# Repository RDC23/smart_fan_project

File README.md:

## Cool Colin - Embedded Systems Smart Fan Project ☀️

**Contributors**: Ross Cathcart, Fraser O'Regan, Ruihang Wang

---

### Overview

This project oversaw the design and construction of a desktop “smart fan” which uses tracking technology to enable the fan to autonomously follow a nearby person, making it ideal for individual use in dynamic workspaces. The tracking mechanism should increase the efficacy in cooling the person by ensuring that it is optimally positioned to promote convective heat loss from the target, reducing heat fatigue and allowing the user to feel more comfortable. 

---

### Project Build

---

### Tracking Mode Demonstration 

https://github.com/RDC23/smart_fan_project/assets/112988260/db7c453c-c118-40b3-909e-dfdff9f8903a

---

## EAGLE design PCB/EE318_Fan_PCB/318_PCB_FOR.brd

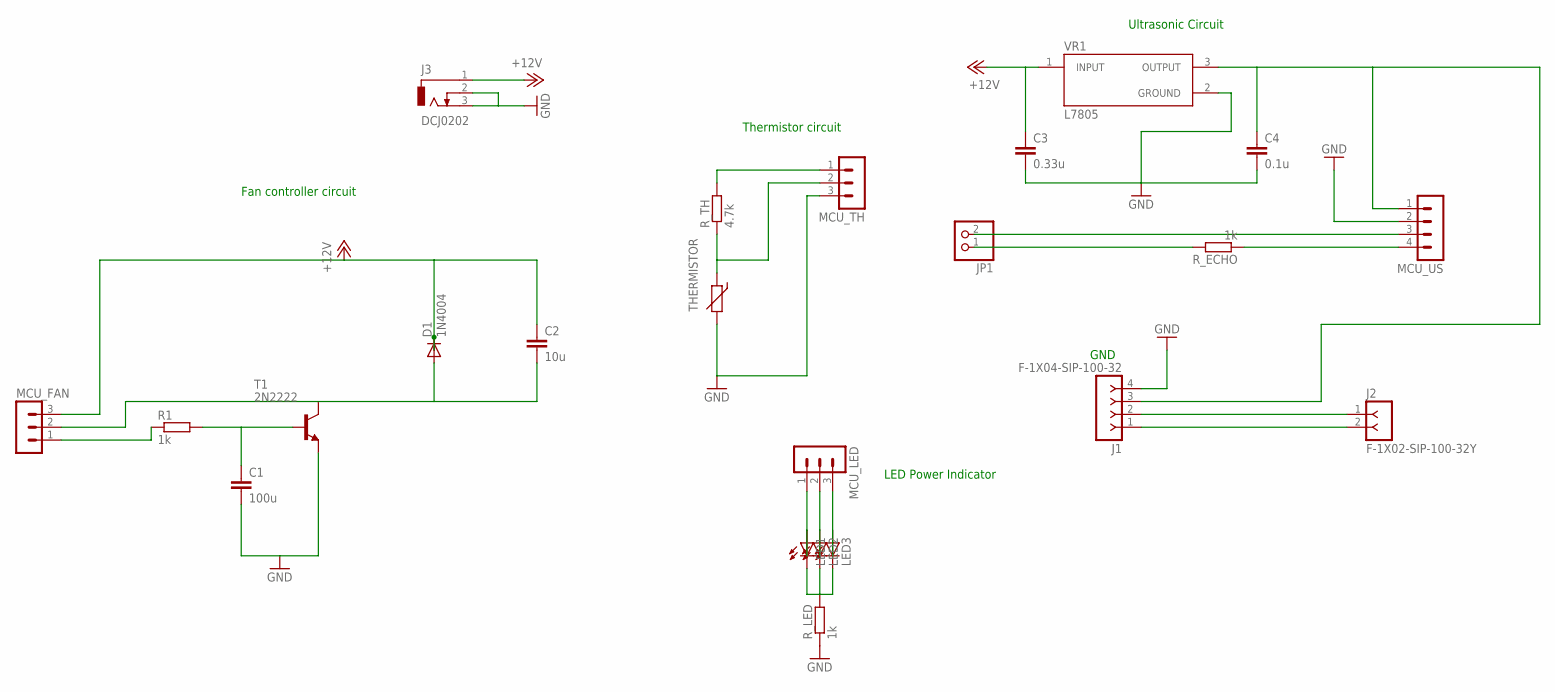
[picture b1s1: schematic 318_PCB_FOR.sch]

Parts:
C1: 100u; C025-025X050
C2: 10u; C025-025X050
C3: 0.33u; C025-025X050
C4: 0.1u; C025-025X050
D1: 1N4004; DO41-10
J1: F-1X04-SIP-100-32; SIP-100-04-32
J2: F-1X02-SIP-100-32Y; SIP-100-02-32Y
J3: DCJ0202
JP1: PINHD-1X2; 1X02
LED1, LED2, LED3: LEDSFH480; SFH480
MCU_FAN: MA03-1
MCU_LED: MA03-1
MCU_TH: MA03-1
MCU_US: MA04-1
R1: 1k; 0207/10
R_ECHO: 1k; 0207/10
R_LED: 1k; 0207/10
R_TH: 4.7k; 0207/10
T1: 2N2222; TO18
THERMISTOR: THERMISTOR-5; R-5
VR1: L7805; TO255P1020X450X2000-3

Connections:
3V3: MCU_TH.1, R_TH.2
+12V: C2.1, C3.1, D1.C, J3.1, MCU_FAN.3, VR1.1 (INPUT)
AMBER: LED2.A, MCU_LED.2
FAN_BLACK: C2.2, D1.A, MCU_FAN.2, T1.3 (C)
GND: C1.2, C3.2, C4.2, J1.4, J3.2, J3.3, MCU_TH.3, MCU_US.2, R_LED.1, T1.1 (E), THERMISTOR.2, VR1.2 (GROUND)
GREEN: LED1.A, MCU_LED.1
unnamed: C1.1, R1.2, T1.2 (B)
unnamed: MCU_US.4, R_ECHO.1
unnamed: LED1.K (C), LED2.K (C), LED3.K (C), R_LED.2
unnamed: JP1.2, MCU_US.3
unnamed: C4.1, J1.3, MCU_US.1, VR1.3 (OUTPUT)
unnamed: JP1.1, R_ECHO.2
unnamed: J1.1, J2.2
unnamed: J1.2, J2.1
P1.6: MCU_FAN.1, R1.1
P8.1: MCU_TH.2, R_TH.1, THERMISTOR.1
RED: LED3.A, MCU_LED.3

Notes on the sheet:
Ultrasonic Circuit
Fan controller circuit
Thermistor circuit
LED Power Indicator
GND

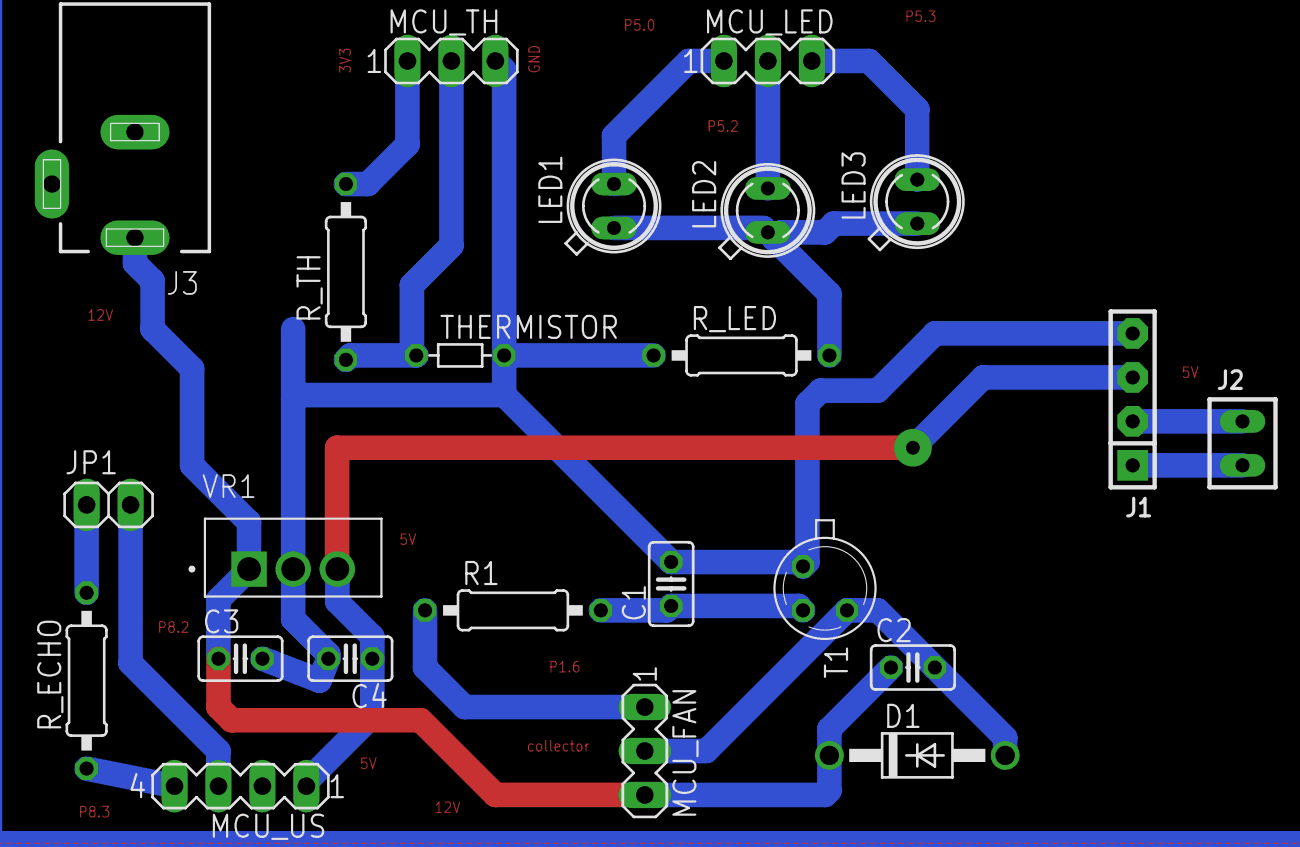
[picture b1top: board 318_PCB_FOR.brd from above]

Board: 2 copper layers, 23 parts (0 on the bottom side), 17 nets.

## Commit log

2024-01-03 setup
2024-01-03 file structure created
2024-01-03 fixed file system
2024-01-09 added servo and ultrasonic libraries
2024-01-21 temp sensor working, mode toggle button and display working
2024-01-21 decoupled isr button for mode toggle into seperate func
2024-01-25 mentor meeting minutes added
2024-01-28 Added external button support and servo integration
2024-01-29 started writing driver for fan pwm
2024-01-31 interfaced a single PIR successfully. FINALLY!
2024-02-02 update servo increment speed
2024-02-03 fixed the upper lower PWM bounds for using mg946r servo
2024-02-04 Update fancontroller.c
    fixed timer ta1ccr2 write from ta0ccr2 since we are using Timer A instance 1
2024-02-04 added servo/fan pwm test code and created a dedicated testing folder
2024-02-04 updated gitignore
2024-02-04 updates gitignore
2024-02-04 fix gi
2024-02-04 gitignore
2024-02-04 ignore all non .h and .c files
2024-02-04 clean filestructure
2024-02-04 gitignore update
2024-02-04 git issue
2024-02-04 added test code
2024-02-05 updated fancontroller driver to attempt to use timer a0 and add in min/ max duty cycles. Needs tested with servo in lab. If it works, write ultility functions to control fan speed at a higher level o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
2024-02-08 fixed servo pwm max value, added startup torque motor func, started decoder driver
2024-02-09 decoder finished
2024-02-10 fan thermo to speed finished. Fan api added extra functions
2024-02-11 added power led support for thermo/fan test code. Fixed ultrasonic pin assignment
2024-02-13 servo code updated so that api keeps track of current angle, not main code. Drafted PIR code. Need to add ultrasonics support
2024-02-15 Update ultrasonic.c
    fix register port to port 8
2024-02-15 Update fancontroller.c
    fixed fan pwm timer setup in fan_init() - it wasn't setting the TA0CTL or TACCR0 before so PWM wasnt working
2024-02-17 working 2 pir and ultrasonic targeting.
2024-02-20 updated fan library to add power calculation function, and hal_LCD to print the power to screen. Both need tested.
2024-02-20 fan.h added
2024-02-21 display code started
2024-02-21 main code started
2024-02-22 updates to main and tidying up libraries
2024-02-22 example display code added for wang
2024-02-22 screen code upload issue
2024-02-23 refactored screen code for MSP430fr4133
2024-02-23 Update thermistor.c
    update thermistor value
2024-02-23 demo (master) code development and bug fixing
2024-02-23 updated screen driver interrupt vector
2024-02-24 button input register and power print fixed. Debounce on on/off button not great
2024-02-25 Update servo.h
    servo delay increased to slow movement
2024-02-27 screen update. not working
2024-02-28 update bruce comments
2024-02-28 fixed i2c interrupt enable. Was using UART one instead! Need to use UCTXIFGn NOT UCTIFG!
2024-02-29 added comments to code and formatted for report
2024-03-01 fixed power calculation function for better precision
2024-03-01 Update i2c.c
    ifg flag changed after Bruce comment
2024-03-06 Screen working using P1.4 and P1.5
2024-03-06 tidied up the code and added comments
2024-03-07 Tidied up the screen code, added comments, and removed unused function, integrated with main code
2024-03-07 file structure clean
2024-03-07 added screen support to main. Issues with screen buffer overflow need fixed
2024-03-12 fixed screen dots issue and printing issues. Added refresh rate support to main to avoid blocking aspect of display. Only update screen after n cycles of main
2024-03-17 Update oled.h
    removed unnecessary defines
2024-03-21 Add files via upload
    added board and schematic files to print
2024-03-29 Update fancontroller.h
    update temp threshold for stability
2024-03-29 updated servo angle (20 to 160 limits), added sdg print and fixed oled issue - oled needs connected at startup of msp to function. Otherwise initialisation commands aren't sent
2024-04-12 modified main.c to only use PIR for detection
2024-04-12 decreased screen refresh rate
2024-04-18 pirs working for basic detection
2024-04-18 ultrasonic and pir working
2024-04-19 updated main to remove the unnecessary pir only funcs
2024-04-30 updated tracking algorithm to improve motion detection.
2024-04-30 added build image
2024-05-03 update tracking
2024-05-05 Update README.md
    added video of track mode

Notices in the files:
parts and their libraries:
con-headers-jp: Copyright (C) 2008, Bob Starr
